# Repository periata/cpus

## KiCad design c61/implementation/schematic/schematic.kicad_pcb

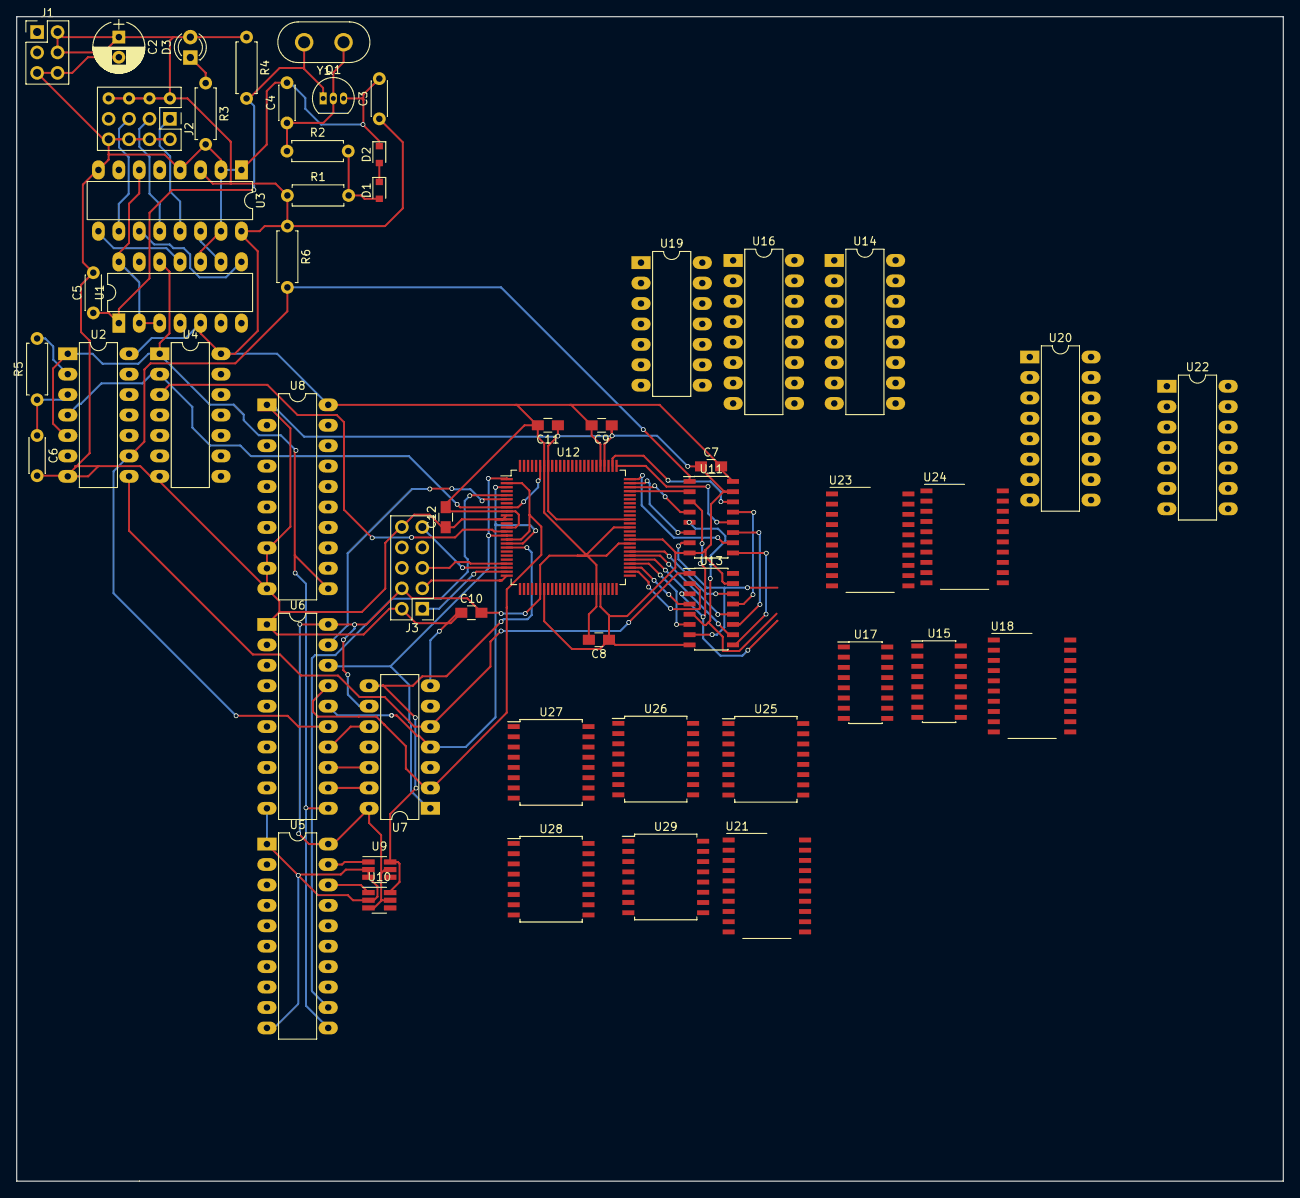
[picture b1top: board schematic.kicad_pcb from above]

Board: 2 copper layers, 157.5 x 144.8 mm, 54 parts (0 on the bottom side), 108 nets.

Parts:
C2: 22u; CP_Radial_D6.3mm_P2.50mm
C3: 100n; C_Disc_D4.3mm_W1.9mm_P5.00mm
C4: 47p; C_Disc_D4.3mm_W1.9mm_P5.00mm
C5: 22p; C_Disc_D4.3mm_W1.9mm_P5.00mm
C6: 10p; C_Disc_D4.3mm_W1.9mm_P5.00mm
C7, C8, C9, C10, C11, C12: 100n; C_0805_HandSoldering
D1, D2: 1N4148; D_0805
D3: LED; LED_D3.0mm
J1: CONN_02X03_PWR; Pin_Header_Straight_2x03_Pitch2.54mm
J2: jumperblock_4; JPArray-03x04-Connected
J3: CONN_02X05; Pin_Header_Straight_2x05_Pitch2.54mm
Q1: BC548A; TO-92_Inline_Narrow_Oval
R1: 2K2; R_Axial_DIN0207_L6.3mm_D2.5mm_P7.62mm_Horizontal
R2: 36K; R_Axial_DIN0207_L6.3mm_D2.5mm_P7.62mm_Horizontal
R3: 100R; R_Axial_DIN0207_L6.3mm_D2.5mm_P7.62mm_Horizontal
R4, R6: 1K; R_Axial_DIN0207_L6.3mm_D2.5mm_P7.62mm_Horizontal
R5: 1K3; R_Axial_DIN0207_L6.3mm_D2.5mm_P7.62mm_Horizontal
U1: 74HC93; DIP-14_W7.62mm_LongPads
U2: 74HC04; DIP-14_W7.62mm_LongPads
U3: 74LS85; DIP-16_W7.62mm_LongPads
U4: 74HC86; DIP-14_W7.62mm_LongPads
U5, U6, U8: 74HC574; DIP-20_W7.62mm_LongPads
U7: 74LS21; DIP-14_W7.62mm_LongPads
U9, U10: 74LVC1G57; SOT-23-6_Handsoldering
U11, U13, U15, U17: 74HC365; SOIC-16_3.9x9.9mm_Pitch1.27mm
U12: EPM240T100C5_REGFILE8X6_V1; TQFP-100_14x14mm_P0.5mm
U14, U16: 74HC283; DIP-16_W7.62mm_LongPads
U18, U21, U23, U24: 74HC244; SO-20_12.8x7.5mm_P1.27mm
U19: 74HC32; DIP-14_W7.62mm_LongPads
U20: 74LS139; DIP-16_W7.62mm_LongPads
U22: 74HC08; DIP-14_W7.62mm_LongPads
U25, U26, U27, U28, U29: 74HC574; SOIC-16W_7.5x10.3mm_Pitch1.27mm
Y1: 24MHz; Crystal_HC50_Vertical

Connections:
3V3: C2.1, C3.1, C7.2, C8.2, C9.2, C10.2, C11.2, C12.2, D3.2, J1.2, J1.4, J2.5, J3.4, R1.1, R4.1, R6.1, U1.5, U2.14, U3.3, U3.16, U4.14, U5.20, U6.20, U7.9, U7.14, U8.20, U9.5, U10.3, U10.5, U11.16, U12.9, U12.13, U12.31, U12.45, U12.59, U12.63, U12.80, U12.94, U13.16, U14.16, U15.16, U16.16, U17.16, U18.20, U19.14, U20.16, U21.20, U22.14, U23.13, U23.20, U24.20
/Instrution Fetch/imm_0: U5.19, U9.1
/Instrution Fetch/imm_1: U5.18, U10.1
/Instrution Fetch/insn_0: U6.14, U7.10
/Instrution Fetch/insn_1: U6.13, U7.12
/Instrution Fetch/insn_2: U6.12, U7.13
/Instrution Fetch/ra0: U6.18, U7.1, U12.1, U12.15
/Instrution Fetch/ra1: U6.17, U7.2, U12.2, U12.16
/Instrution Fetch/ra2: U6.16, U7.4, U12.3, U12.17
/Instrution Fetch/ra_sel_inv: U2.8, U7.5, U13.1
/Instrution Fetch/rb1: U5.12, U12.5
/Instrution Fetch/rb2: U6.19, U12.6
/Pipeline st 1 latches/d_extcarrys1: U18.9, U21.9, U23.9, U24.9, U29.8
/Pipeline st 1 latches/d_exts1: U2.11, U7.8, U9.6, U10.6, U12.18, U15.1, U15.15, U19.2, U29.3
/Pipeline st 1 latches/d_isjmps1: U7.6, U25.7
/Pipeline st 1 latches/d_membases10: U12.40, U24.2, U27.4
/Pipeline st 1 latches/d_membases11: U12.41, U24.4, U27.5
/Pipeline st 1 latches/d_membases12: U12.48, U24.6, U27.6
/Pipeline st 1 latches/d_membases13: U12.49, U24.8, U27.7
/Pipeline st 1 latches/d_membases14: U12.50, U24.17, U27.8
/Pipeline st 1 latches/d_membases15: U12.51, U24.15, U27.9
/Pipeline st 1 latches/d_rasrcs10: U18.18, U21.18, U23.18, U24.18, U26.6
/Pipeline st 1 latches/d_rasrcs11: U18.16, U21.16, U23.16, U24.16, U26.7
/Pipeline st 1 latches/d_rasrcs12: U18.14, U21.14, U23.14, U24.14, U26.8
/Pipeline st 1 latches/d_rasrcs13: U18.12, U21.12, U23.12, U24.12, U26.9
/Pipeline st 1 latches/d_rasrcs14: U18.3, U21.3, U23.3, U24.3, U27.2
/Pipeline st 1 latches/d_rasrcs15: U18.5, U21.5, U23.5, U24.5, U27.3
/Pipeline st 1 latches/d_ravals10: U11.3, U13.3, U18.2, U21.11, U28.2
/Pipeline st 1 latches/d_ravals11: U11.5, U13.5, U18.4, U21.2, U28.3
/Pipeline st 1 latches/d_ravals12: U11.7, U13.7, U18.6, U21.4, U28.4
/Pipeline st 1 latches/d_ravals13: U11.9, U13.9, U18.8, U21.6, U28.5
/Pipeline st 1 latches/d_ravals14: U11.11, U13.11, U18.17, U21.8, U28.6
/Pipeline st 1 latches/d_ravals15: U11.13, U13.13, U18.15, U21.17, U28.7
/Pipeline st 1 latches/d_rbims10: U15.3, U17.3, U25.8
/Pipeline st 1 latches/d_rbims11: U15.5, U17.5, U25.9
/Pipeline st 1 latches/d_rbims12: U15.7, U17.7, U26.2
/Pipeline st 1 latches/d_rbims13: U15.9, U17.9, U26.3
/Pipeline st 1 latches/d_rbims14: U15.11, U17.11, U26.4
/Pipeline st 1 latches/d_rbims15: U15.13, U17.13, U26.5
/d_dsts13: R6.2, U2.9, U6.15, U11.1
/pipeline st. 1 alu/mux//op_ext: U2.10, U17.1, U17.15, U22.2
/pipeline st. 1 alu/mux/carry_incr: U16.13, U23.11
/pipeline st. 1 alu/mux/imm0: U14.6, U17.2, U19.1
/pipeline st. 1 alu/mux/imm1: U14.2, U17.4, U22.1
/pipeline st. 1 alu/mux/imm2: U14.15, U17.6
/pipeline st. 1 alu/mux/imm3: U14.11, U17.10
/pipeline st. 1 alu/mux/imm4: U16.6, U17.12
/pipeline st. 1 alu/mux/imm5: U16.2, U17.14
/pipeline st. 1 alu/mux/oas_ra: U18.1, U18.19, U20.4
/pipeline st. 1 alu/mux/oas_ra0i: U20.5, U23.1, U23.19
/pipeline st. 1 alu/mux/oas_rash: U20.7, U21.1, U21.19
/pipeline st. 1 alu/mux/oas_rb1: U20.6, U24.1, U24.19
/pipeline st. 1 alu/mux/raqi0: U12.82, U23.2
/pipeline st. 1 alu/mux/raqi1: U12.83, U23.4
/pipeline st. 1 alu/mux/raqi2: U12.84, U23.6
/pipeline st. 1 alu/mux/raqi3: U12.85, U23.8
/pipeline st. 1 alu/mux/raqi4: U12.86, U23.17
/pipeline st. 1 alu/mux/raqi5: U12.87, U23.15
/pipeline st. 1 alu/mux/rb0q0: U12.66, U14.5
/pipeline st. 1 alu/mux/rb0q1: U12.67, U14.3
/pipeline st. 1 alu/mux/rb0q2: U12.68, U14.14
/pipeline st. 1 alu/mux/rb0q3: U12.69, U14.12
/pipeline st. 1 alu/mux/rb0q4: U12.70, U16.5
/pipeline st. 1 alu/mux/rb0q5: U12.71, U16.3
/registers/op mux/ra0q0: U11.2, U12.72
/registers/op mux/ra0q1: U11.4, U12.73
/registers/op mux/ra0q2: U11.6, U12.74
/registers/op mux/ra0q3: U11.10, U12.75
/registers/op mux/ra0q4: U11.12, U12.76
/registers/op mux/ra0q5: U11.14, U12.77
GND: C2.2, C3.2, C4.2, C5.2, C6.2, C7.1, C8.1, C9.1, C10.1, C11.1, C12.1, D2.1, J1.5, J1.6, J2.6, J3.2, J3.10, Q1.3, R3.2, U1.10, U2.7, U3.1, U3.2, U3.4, U3.8, U3.15, U4.7, U5.1, U5.10, U6.1, U6.10, U7.7, U8.1, U8.8, U8.9, U8.10, U9.2, U9.3, U10.2, U11.8, U11.15, U12.10, U12.11, U12.32, U12.46, U12.60, U12.65, U12.79, U12.93, U13.8, U13.15, U14.7, U14.8, U15.8, U16.8, U16.11, U16.12, U16.14, U16.15, U17.8, U18.10, U18.11, U18.13, U19.7, U20.1, U20.8, U21.10, U21.13, U21.15, U22.7, U23.10, U24.10, U24.11, U24.13, U25.1, U25.10, U26.1, U26.10, U27.1, U27.10, U28.1, U28.10, U29.1, U29.9, U29.10
unnamed: C4.1, Q1.2, R2.1, Y1.1
unnamed: C5.1, Q1.1, R4.2, U1.1, Y1.2
unnamed: C6.1, R5.1, U2.3
unnamed: D1.1, D2.2
unnamed: D1.2, R1.2, R2.2
unnamed: D3.1, R3.1
unnamed: J2.1, U3.13
unnamed: J2.2, U3.12
unnamed: J2.3, U3.10
unnamed: J3.1, U12.24
unnamed: J3.3, U12.25
unnamed: J3.5, U12.22
unnamed: J3.9, U12.23
unnamed: R5.2, U2.2
unnamed: U1.8, U3.11
unnamed: U1.9, U3.14
unnamed: U1.11, U3.9
unnamed: U1.2, U1.3, U1.14, U3.6
unnamed: U12.52, U13.2
unnamed: U12.53, U13.4
unnamed: U12.54, U13.6
unnamed: U12.55, U13.10
unnamed: U12.56, U13.12
unnamed: U12.57, U13.14
unnamed: U14.1, U15.4
unnamed: U14.4, U15.2
unnamed: U14.9, U16.7
unnamed: U14.10, U15.10
unnamed: U14.13, U15.6
unnamed: U15.12, U16.4
unnamed: U15.14, U16.1
unnamed: U19.3, U20.2
unnamed: U20.3, U22.3
clk0: U1.12, U2.1, U2.5, U4.1, U5.11, U6.11, U8.11
clk0del: U2.4, U4.2, U12.8, U12.95
clk1: U2.6, U25.11, U26.11, U27.11, U28.11, U29.11
clk_edge: U4.3, U12.14

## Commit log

2018-06-05 initial version
2018-06-07 Test program exercising all basic instructions runs correctly
2018-06-12 Finish adding instructions; implementation of ALU for use in a GAL16V8
    (needs verification that the logic actually fits, but I think it should)
2018-06-20 add CPLD implementation of register banks
2018-06-21 update register file; add cpld version of alu
2018-08-10 initial version of c61 schematic (incomplete)
2018-09-01 More work on C61 schematic
2018-09-02 aborted start of io processor design
2018-09-22 remove backup files
2018-09-22 C61 ALU: JEDEC file for burning PALs (untested)
2018-09-22 C61: more updates to schematic
2018-09-22 Starting work on a verilog implementation of IO881
2018-09-22 more tests for fifo, highlighting a failure
2018-09-22 fix failing fifo test
2018-09-22 async producer/consumer test for fifo
2018-09-22 io881: reset input to fifo
2018-09-24 don't track .vpi files
2018-09-24 io881: ram module
2018-10-06 beginning work on instruction fetch work abandoned due to switch to ram-based registers
2018-10-06 remove register file - to be replaced with a double speed RAM
2018-10-08 update interface for instruction fetcher; begin implementation
2018-10-16 More development on instruction fetch
2018-10-18 track task load state; correctly handle jump targets; fetch new insn after jump
2018-10-18 handle instruction decode of first opcode in word with no operands
2018-10-19 handle second instruction in packed words; update state for PULL instructions
